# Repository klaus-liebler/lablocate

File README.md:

# Lieblers LabLocate

## Components 
- Quovo DWM3000 ist ein UWB-Ortungsmodul (UltaWideBand_ige Funkwellen lassen sich gut hinsichtlich Signallaufzeit vermessen)
- ESP32-C6: Mikrocontroller mit 2.4 GHz Wi-Fi 6 (802.11ax), Bluetooth® 5 (LE), Zigbee and Thread (802.15.4)
- LSM6DS3 ist ein 6DOF-Beschleunigungssensor
- TPS63802 ist ein StepUp-Step-Down-Converter
- TP4057 ist ein Batterie-Lade-ID

## Recommendations
- Needs https://github.com/klaus-liebler/kicad-libs
- Recommended PCB Software: [https://www.kicad.org](https://www.kicad.org/)
- Recommended PCBA Service: https://jlcpcb.com/
- Recommended Kicad-Plugin for JLCPCB: https://github.com/Bouni/kicad-jlcpcb-tools
- Check this Software for UWB Locating: https://github.com/jremington/UWB-Indoor-Localization_Arduino

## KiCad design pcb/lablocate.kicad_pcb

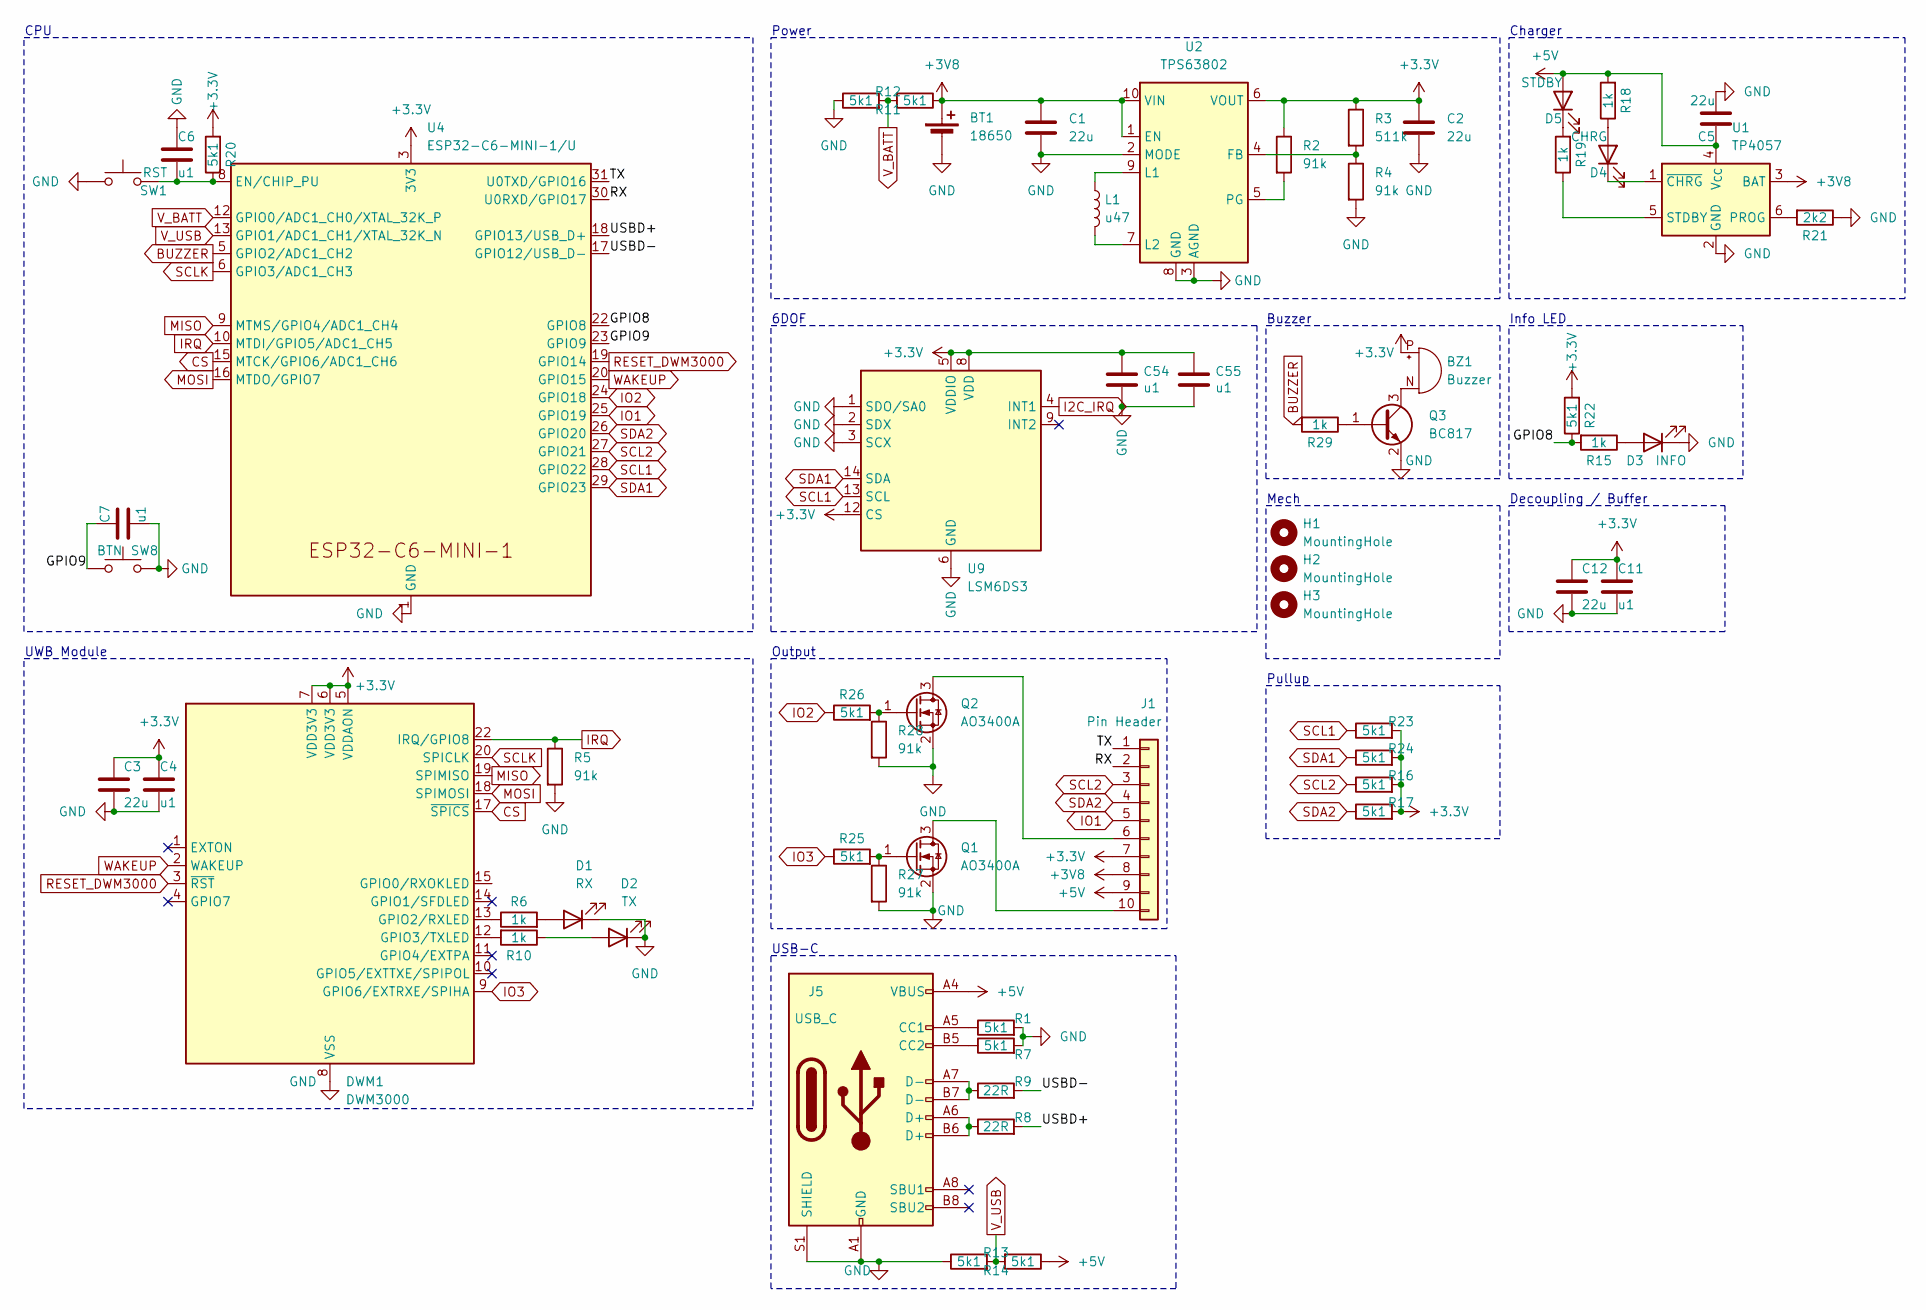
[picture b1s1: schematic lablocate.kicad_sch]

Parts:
BT1: 18650; BatteryHolder_MPD_BH-18650-PC2
BZ1: Buzzer; XDCR_CMT-7525-80-SMT-TR_handsolder
C1, C2, C3, C5, C12: 22u; C_0603_1608Metric
C4, C6, C7, C11: u1; C_0201_0603Metric
C54, C55: u1; C_0201_0603Metric; MPN GRM033R61A104KE15D
D1: RX; LED_0402_1005Metric
D2: TX; LED_0402_1005Metric
D3: INFO; LED_0402_1005Metric
D4: CHRG; LED_0402_1005Metric
D5: STDBY; LED_0402_1005Metric
DWM1: DWM3000; DWM1000
H1, H2, H3: MountingHole; MountingHole_2.2mm_M2
J1: Pin Header; PinHeader_1x10_P2.54mm_Vertical
J5: USB_C; USB_C_Receptacle_HRO_TYPE-C-31-M-12
L1: u47; L_Changjiang_FTC252012S
Q1, Q2: AO3400A; SOT-23
Q3: BC817; SOT-23
R1, R7, R11, R12, R13, R14, R16, R17, R20, R22, R23, R24, R25, R26: 5k1; R_0201_0603Metric
R2, R4, R5, R27, R28: 91k; R_0201_0603Metric
R3: 511k; R_0201_0603Metric
R6, R10, R15, R18, R19, R29: 1k; R_0402_1005Metric
R8, R9: 22R; R_0402_1005Metric
R21: 2k2; R_0402_1005Metric
SW1: RST; SW_SPST_B3U-1000P; MPN TS-1095E-A6B3-D2
SW8: BTN; SW_SPST_B3U-1000P; MPN TS-1095E-A6B3-D2
U1: TP4057; TSOT-23-6
U2: TPS63802; DLA0010A
U4: ESP32-C6-MINI-1/U; ESP32-C6-MINI-1
U9: LSM6DS3; LGA-14_3x2.5mm_P0.5mm_LayoutBorder3x4y; MPN LSM6DS3TR-C

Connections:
+3.3V: BZ1.P (+), C2.1, C3.1, C4.1, C11.1, C12.1, C54.2, C55.2, DWM1.5 (VDDAON), DWM1.6 (VDD3V3), DWM1.7 (VDD3V3), J1.7, R2.1, R3.1, R16.2, R17.2, R20.2, R22.2, R23.2, R24.2, U2.6 (VOUT), U4.3 (3V3), U9.5 (VDDIO), U9.8 (VDD), U9.12 (CS)
+3V8: BT1.1 (+), C1.1, J1.8, R12.1, U1.3 (BAT), U2.1 (EN), U2.10 (VIN)
+5V: C5.1, D5.2 (A), J1.9, J5.A4 (VBUS), J5.A9 (VBUS), J5.B4 (VBUS), J5.B9 (VBUS), R13.1, R18.2, U1.4 (V_{CC})
/GPIO8: R15.2, R22.1, U4.22 (GPIO8)
/GPIO9: C7.1, SW8.1, U4.23 (GPIO9)
/RX: J1.2, U4.30 (U0RXD/GPIO17)
/TX: J1.1, U4.31 (U0TXD/GPIO16)
/USBD+: R8.2, U4.18 (GPIO13/USB_D+)
/USBD-: R9.2, U4.17 (GPIO12/USB_D-)
BUZZER: R29.2, U4.5 (GPIO2/ADC1_CH2)
CS: DWM1.17 (~SPICS), U4.15 (MTCK/GPIO6/ADC1_CH6)
GND: BT1.2 (-), C1.2, C2.2, C3.2, C4.2, C5.2, C6.1, C7.2, C11.2, C12.2, C54.1, C55.1, D1.1 (K), D2.1 (K), D3.1 (K), DWM1.8 (VSS), DWM1.16 (VSS), DWM1.21 (VSS), DWM1.23 (VSS), DWM1.24 (VSS), J5.A1 (GND), J5.A12 (GND), J5.B1 (GND), J5.B12 (GND), J5.S1 (SHIELD), Q1.2 (S), Q2.2 (S), Q3.2 (E), R1.2, R4.2, R5.2, R7.2, R11.1, R14.1, R21.1, R27.2, R28.2, SW1.1, SW8.2, U1.2 (GND), U2.2 (MODE), U2.3 (AGND), U2.8 (GND), U4.1 (GND), U4.2 (GND), U4.11 (GND), U4.14 (GND), U4.36 (GND), U4.37 (GND), U4.38 (GND), U4.39 (GND), U4.40 (GND), U4.41 (GND), U4.42 (GND), U4.43 (GND), U4.44 (GND), U4.45 (GND), U4.46 (GND), U4.47 (GND), U4.48 (GND), U4.49 (GND), U4.50 (GND), U4.51 (GND), U4.52 (GND), U4.53 (GND), U9.1 (SDO/SA0), U9.2 (SDX), U9.3 (SCX), U9.6 (GND), U9.7 (GND)
I2C_IRQ: U9.4 (INT1)
IO1: J1.5, U4.25 (GPIO19)
IO2: R26.1, U4.24 (GPIO18)
IO3: DWM1.9 (GPIO6/EXTRXE/SPIHA), R25.1
IRQ: DWM1.22 (IRQ/GPIO8), R5.1, U4.10 (MTDI/GPIO5/ADC1_CH5)
MISO: DWM1.19 (SPIMISO), U4.9 (MTMS/GPIO4/ADC1_CH4)
MOSI: DWM1.18 (SPIMOSI), U4.16 (MTDO/GPIO7)
unnamed: BZ1.N (-), Q3.3 (C)
unnamed: D1.2 (A), R6.2
unnamed: D2.2 (A), R10.1
unnamed: D3.2 (A), R15.1
unnamed: D4.2 (A), R18.1
unnamed: D4.1 (K), U1.1 (~CHRG)
unnamed: D5.1 (K), R19.2
unnamed: DWM1.13 (GPIO2/RXLED), R6.1
unnamed: DWM1.12 (GPIO3/TXLED), R10.2
unnamed: J1.6, Q2.3 (D)
unnamed: J1.10, Q1.3 (D)
unnamed: J5.A5 (CC1), R1.1
unnamed: J5.B5 (CC2), R7.1
unnamed: J5.A6 (D+), J5.B6 (D+), R8.1
unnamed: J5.A7 (D-), J5.B7 (D-), R9.1
unnamed: Q1.1 (G), R25.2, R27.1
unnamed: Q2.1 (G), R26.2, R28.1
unnamed: Q3.1 (B), R29.1
unnamed: R21.2, U1.6 (PROG)
unnamed: R19.1, U1.5 (STDBY)
unnamed: R3.2, R4.1, U2.4 (FB)
unnamed: L1.1, U2.9 (L1)
unnamed: L1.2, U2.7 (L2)
unnamed: R2.2, U2.5 (PG)
unnamed: C6.2, R20.1, SW1.2, U4.8 (EN/CHIP_PU)
RESET_DWM3000: DWM1.3 (~RST), U4.19 (GPIO14)
SCL1: R23.1, U4.28 (GPIO22), U9.13 (SCL)
SCL2: J1.3, R16.1, U4.27 (GPIO21)
SCLK: DWM1.20 (SPICLK), U4.6 (GPIO3/ADC1_CH3)
SDA1: R24.1, U4.29 (GPIO23), U9.14 (SDA)
SDA2: J1.4, R17.1, U4.26 (GPIO20)
V_BATT: R11.2, R12.2, U4.12 (GPIO0/ADC1_CH0/XTAL_32K_P)
V_USB: R13.2, R14.2, U4.13 (GPIO1/ADC1_CH1/XTAL_32K_N)
WAKEUP: DWM1.2 (WAKEUP), U4.20 (GPIO15)

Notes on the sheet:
Buzzer
Info LED
6DOF
Decoupling / Buffer
Output
Charger
Pullup
CPU
Mech
UWB Module
Power
USB-C

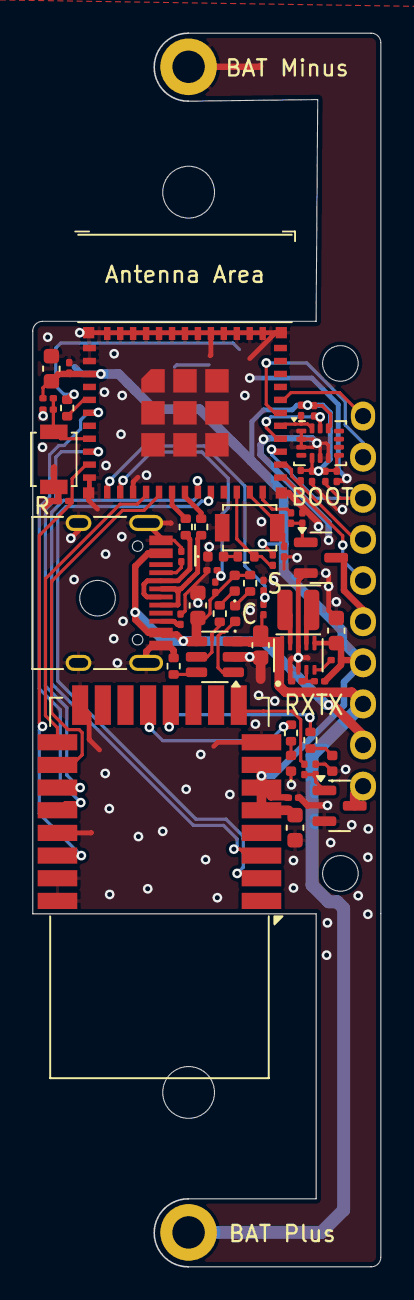
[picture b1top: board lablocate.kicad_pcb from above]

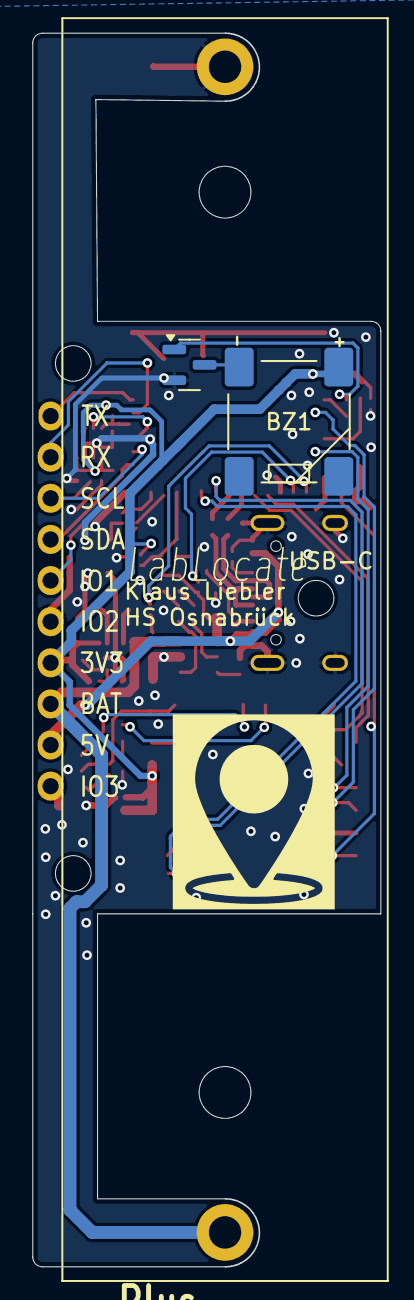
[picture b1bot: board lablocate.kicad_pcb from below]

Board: 2 copper layers, 21.5 x 76.2 mm, 63 parts (5 on the bottom side), 52 nets.

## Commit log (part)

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2026-03-20 Initial
2026-03-20 Create README.md with project overview and resources
    Added initial README content with project details and recommendations.
